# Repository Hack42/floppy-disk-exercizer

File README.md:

# floppy-disk-exercizer

> [!WARNING]
> This repository is moved to <https://codeberg.org/ComputerMuseum/floppy-disk-exercizer> and archived.

Tool to check mechanical functionality of a floppy disk drive with an arduino

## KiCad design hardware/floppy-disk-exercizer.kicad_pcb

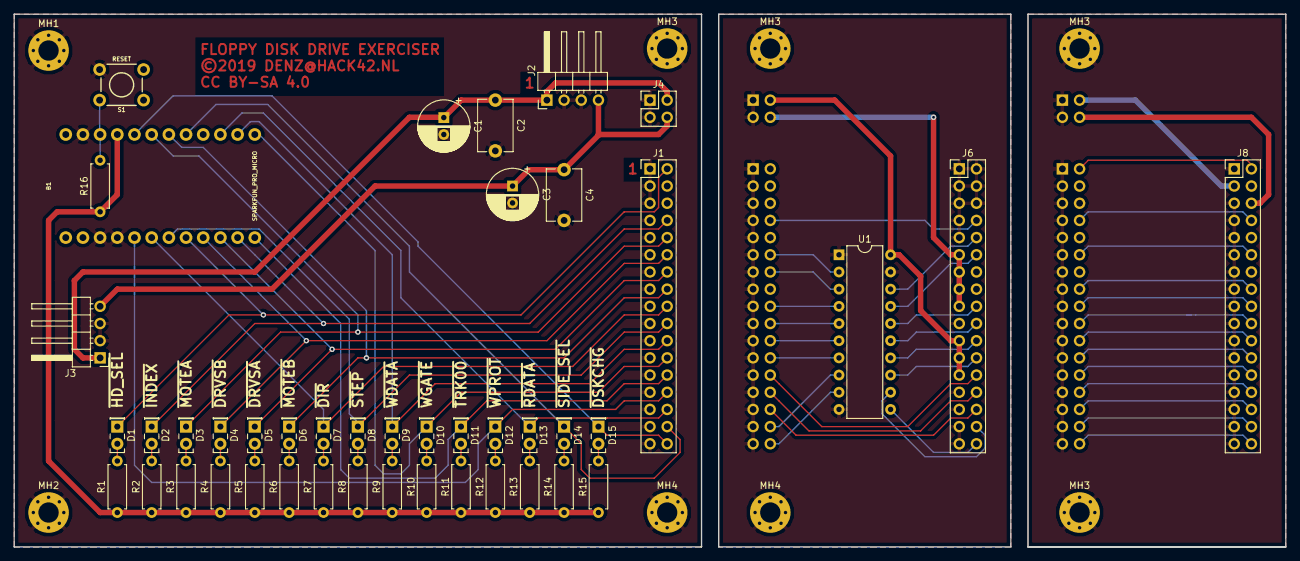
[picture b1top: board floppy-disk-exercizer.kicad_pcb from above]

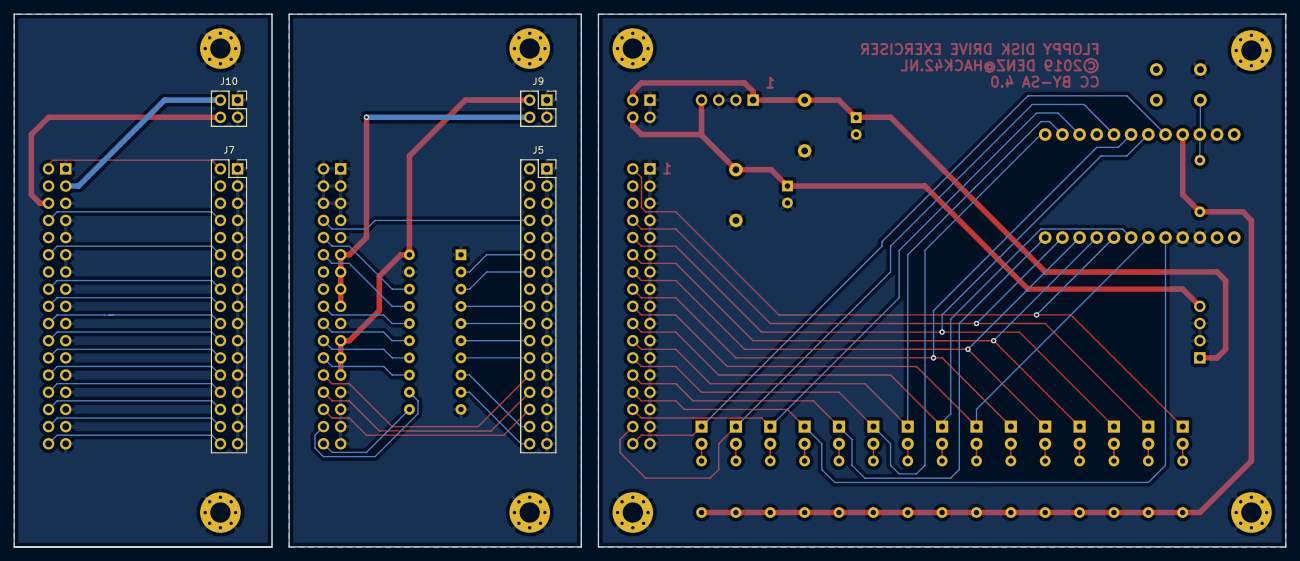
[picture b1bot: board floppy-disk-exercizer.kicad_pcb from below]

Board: 2 copper layers, 188.0 x 78.7 mm, 56 parts (4 on the bottom side), 68 nets.

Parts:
B1: SPARKFUN_PRO_MICRO
C1, C3: CP; CP_Radial_D7.5mm_P2.50mm
C2, C4: C; C_Disc_D7.5mm_W5.0mm_P7.50mm
D1, D2, D3, D4, D5, D6, D7, D8, D9, D10, D11, D12, D13, D14, D15: LED; LED_Rectangular_W5.0mm_H2.0mm
J1, J6, J8: Conn_02x17_Odd_Even; PinHeader_2x17_P2.54mm_Vertical
J2, J3: Conn_01x04; PinHeader_1x04_P2.54mm_Horizontal
J4: Conn_02x02_Odd_Even; PinHeader_2x02_P2.54mm_Vertical
J5, J7: Conn_02x17_Odd_Even; PinSocket_2x17_P2.54mm_Vertical
J9, J10: Conn_02x02_Odd_Even; PinSocket_2x02_P2.54mm_Vertical
MH1, MH2, MH3, MH3#2, MH3#3, MH3#4, MH4, MH4#2: MountingHole_Pad; MountingHole_3mm_Pad_Via
R1, R2, R3, R4, R5, R6, R7, R8, R9, R10, R11, R12, R13, R14, R15: 390; R_Axial_DIN0207_L6.3mm_D2.5mm_P7.62mm_Horizontal
R16: 10k; R_Axial_DIN0207_L6.3mm_D2.5mm_P7.62mm_Horizontal
S1: RESET; TACTILE_SWITCH_PTH_6.0MM
U1: 74LS541; DIP-20_W7.62mm

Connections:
+5V: C1.1, C2.1, J2.1, J3.1, J4.2, J6.21, J6.23, J6.25, J8.3, J9.2, J10.2, U1.20
+12V: C3.1, C4.1, J2.4, J3.4, J4.4, J6.11, J6.13, J6.15, J6.17, J8.6, J9.4, J10.4
/adapters/~DIRo: J5.18, U1.4
/adapters/~DIRp: J7.18, J8.18
/adapters/~DRVSAo: J5.14, U1.3
/adapters/~DRVSBo: J5.12, U1.2
/adapters/~DRVSBp: J7.12, J8.12
/adapters/~DSKCHGp: J7.34, J8.34
/adapters/~HD_SELp: J7.2, J8.2
/adapters/~INDEXo: J5.8, J6.8
/adapters/~INDEXp: J7.8, J8.8
/adapters/~LATEo: J5.34, U1.9
/adapters/~MOTEBp: J7.16, J8.16
/adapters/~RDATAo: J5.30, J6.30
/adapters/~RDATAp: J7.30, J8.30
/adapters/~SIDE_SELo: J5.32, U1.8
/adapters/~SIDE_SELp: J7.32, J8.32
/adapters/~STEPo: J5.20, U1.5
/adapters/~STEPp: J7.20, J8.20
/adapters/~TRK00o: J5.26, J6.26
/adapters/~TRK00p: J7.26, J8.26
/adapters/~WDATAo: J5.22, U1.6
/adapters/~WDATAp: J7.22, J8.22
/adapters/~WGATEo: J5.24, U1.7
/adapters/~WGATEp: J7.24, J8.24
/adapters/~WPROTo: J5.28, J6.28
/adapters/~WPROTp: J7.28, J8.28
/lWDATA: D9.2, R9.2
GND: B1.3, B1.4, B1.23, C1.2, C2.2, C3.2, C4.2, J1.1, J1.3, J1.5, J1.7, J1.9, J1.11, J1.13, J1.15, J1.17, J1.19, J1.21, J1.23, J1.25, J1.27, J1.29, J1.31, J1.33, J2.2, J2.3, J3.2, J3.3, J4.1, J4.3, J5.1, J5.3, J5.5, J5.7, J5.9, J5.11, J5.13, J5.15, J5.17, J5.19, J5.21, J5.23, J5.25, J5.27, J5.29, J5.31, J5.33, J6.1, J6.2, J6.3, J6.4, J6.5, J6.6, J6.7, J6.9, J6.19, J6.27, J6.29, J6.31, J6.33, J7.1, J7.3, J7.5, J7.7, J7.9, J7.11, J7.13, J7.15, J7.17, J7.19, J7.21, J7.23, J7.25, J7.27, J7.29, J7.31, J7.33, J8.1, J8.5, J8.7, J8.9, J8.11, J8.13, J8.15, J8.17, J8.19, J8.21, J8.23, J8.25, J8.27, J8.29, J8.31, J8.33, J9.1, J9.3, J10.1, J10.3, MH1.1, MH2.1, MH3.1, MH3#2.1, MH3#3.1, MH3#4.1, MH4.1, MH4#2.1, S1.4, U1.1, U1.10, U1.19
unnamed: B1.22, R16.2, S1.2
unnamed: D1.2, R1.2
unnamed: D2.2, R2.2
unnamed: D3.2, R3.2
unnamed: D4.2, R4.2
unnamed: D5.2, R5.2
unnamed: D6.2, R6.2
unnamed: D7.2, R7.2
unnamed: D8.2, R8.2
unnamed: D10.2, R10.2
unnamed: D11.2, R11.2
unnamed: D12.2, R12.2
unnamed: D13.2, R13.2
unnamed: D14.2, R14.2
unnamed: D15.2, R15.2
unnamed: J6.10, U1.18
unnamed: J6.12, U1.17
unnamed: J6.18, U1.16
unnamed: J6.20, U1.15
unnamed: J6.22, U1.14
unnamed: J6.24, U1.13
unnamed: J6.32, U1.12
unnamed: J6.34, U1.11
VCC: B1.21, R1.1, R2.1, R3.1, R4.1, R5.1, R6.1, R7.1, R8.1, R9.1, R10.1, R11.1, R12.1, R13.1, R14.1, R15.1, R16.1
~DIR: B1.6, D7.1, J1.18
~DRVSA: B1.10, D5.1, J1.14
~DRVSB: B1.9, D4.1, J1.12
~DSKCHG: B1.20, D15.1, J1.34
~HD_SEL: B1.8, D1.1, J1.2
~INDEX: B1.11, D2.1, J1.8
~MOTEA: B1.19, D3.1, J1.10
~MOTEB: B1.18, D6.1, J1.16
~RDATA: B1.15, D13.1, J1.30
~SIDE_SEL: B1.17, D14.1, J1.32
~STEP: B1.7, D8.1, J1.20
~TRK00: B1.12, D11.1, J1.26
~WDATA: B1.14, D9.1, J1.22
~WGATE: B1.13, D10.1, J1.24
~WPROT: B1.5, D12.1, J1.28

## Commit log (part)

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2019-10-11 pinout text added
2019-11-08 beginnetje gemaakt
2019-11-09 verschoven in juiste directories, hardware toegevoegd
2019-11-09 Notities rond de firmware

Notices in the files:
hardware/floppy-disk-exercizer.kicad_pcb:
©2019 DENZ@HACK42.NL
CC BY-SA 4.0
